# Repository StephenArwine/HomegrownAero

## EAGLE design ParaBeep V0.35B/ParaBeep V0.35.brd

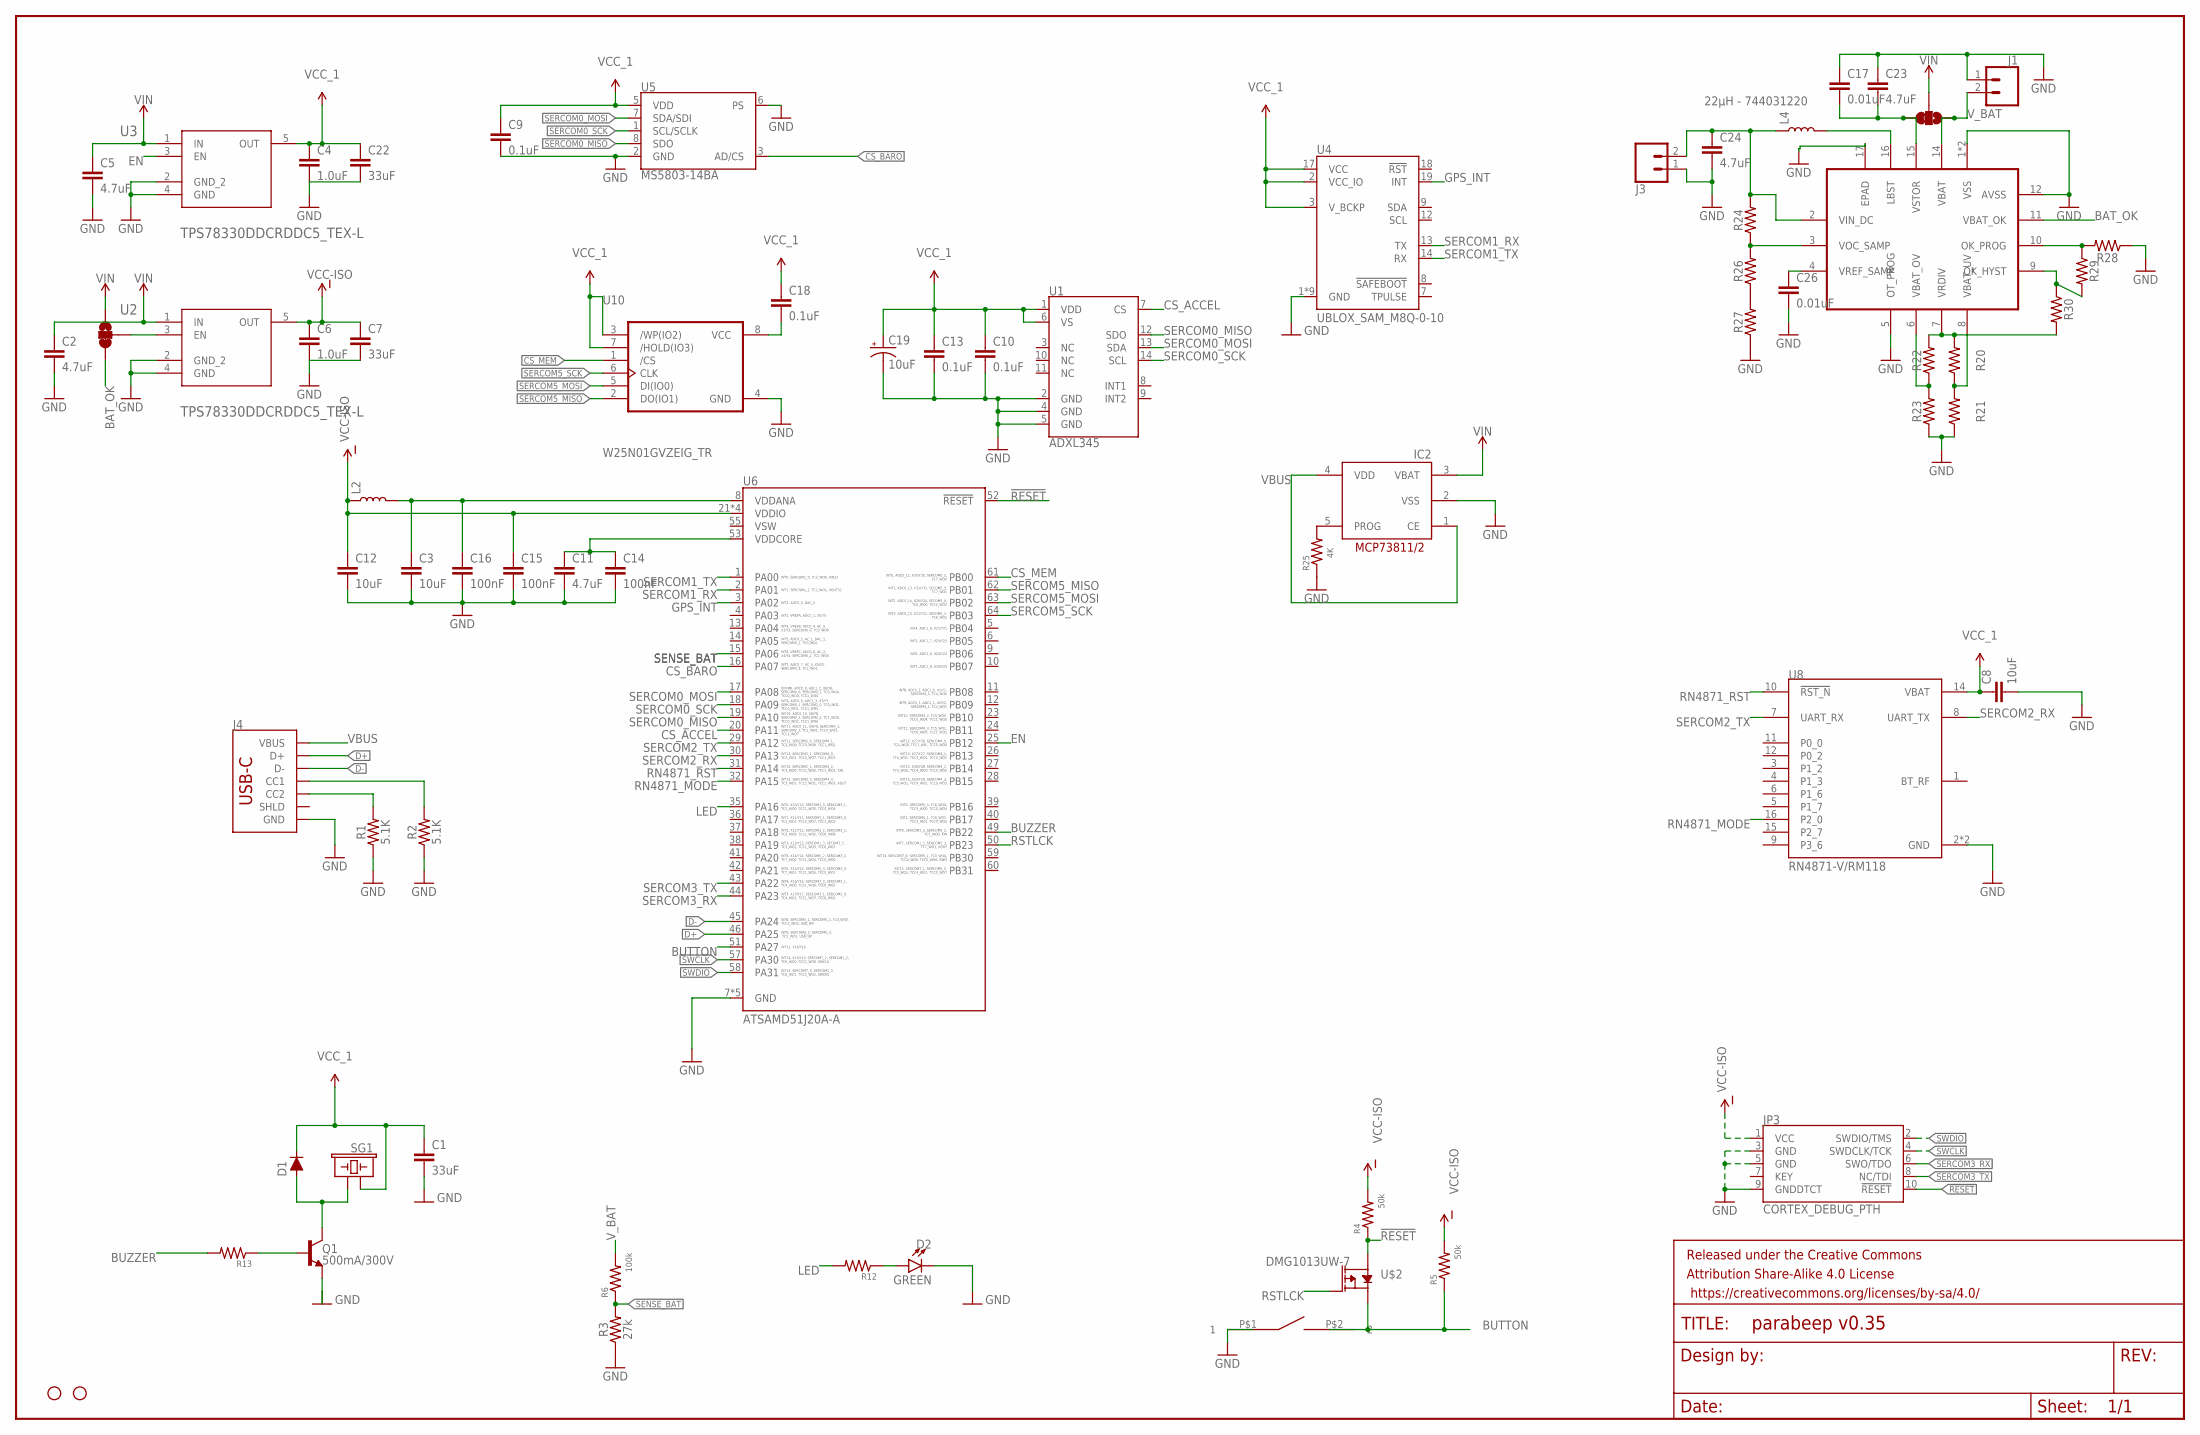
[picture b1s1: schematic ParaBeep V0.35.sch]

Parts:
C1, C7, C22: 33uF; 1206
C2, C5, C11, C24: 4.7uF; 0603
C3, C8, C12: 10uF; 0603
C4, C6: 1.0uF; 0603
C9, C10, C13, C18: 0.1uF; 0603
C14, C15, C16: 100nF; 0603
C17, C26: 0.01uF; 0402
C19: 10uF; EIA3216
C23: 4.7uF; 0402
D1: 250mA/100V; SOD-323
D2: GREEN; LED-0603
FRAME1: FRAME-LEDGER; CREATIVE_COMMONS
H1, H2: STAND-OFFTIGHT; STAND-OFF-TIGHT
IC2: MCP73811/2; SOT23-5L
J1, J3: CONN_02-JST-2MM-SMT; JST-2-SMD
J4: USB_C_2-LAYER_PADS; USB-C-16P-2LAYER-PADS
JP1, JP2: JUMPER-SMT_3_1-NC_TRACE_SILK; SMT-JUMPER_3_1-NC_TRACE_SILK
JP3: CORTEX_DEBUG_PTH; 2X5-PTH-1.27MM
L2: INDUCTORFB-30OHM; 0603
L4: 22µH - 744031220; INDUCTOR_4.7UH
Q1: 500mA/300V; SOT23-3
R1, R2: 5.1K; 0402
R3: 27k; 0402
R4, R5: 50k; 0402
R6: 100k; 0402
R12, R13, R20, R21, R22, R23, R24, R26, R27, R28, R29, R30: 0402
R25: 4K; 0402
SG1: BUZZER-SMD_KIT; BUZZER-CCV-KIT
U1: ADXL345; LGA-14
U2, U3: TPS78330DDCRDDC5_TEX-L; DDC5_TEX-L
U4: UBLOX_SAM_M8Q-0-10; SAM-M8Q
U5: MS5803-14BA; MS5803
U6: ATSAMD51J20A-A; TQFP64
U8: RN4871-V/RM118; XCVR_RN4871-V/RM118
U9: BQ25504RGTR; QFN50P300X300X100-17N
U10: W25N01GVZEIG_TR; SON127P800X600X80-9N
U$2: DMG1013UW-7
U$3: AB11AH-HC

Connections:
!RESET: JP3.10 (!RESET), R4.1, U6.52 (!RESET), U$2.2 (S)
BAT_OK: JP2.3, U9.11 (VBAT_OK)
BUTTON: R5.1, U6.51 (PA27), U$2.3 (D), U$3.P$2 (2)
BUZZER: R13.2, U6.49 (PB22)
CS_ACCEL: U1.7 (CS), U6.20 (PA11)
CS_BARO: U5.3 (AD/CS), U6.16 (PA07)
CS_MEM: U6.61 (PB00), U10.1 (/CS)
D+: J4.A6 (D+), J4.B6 (D+), U6.46 (PA25)
D-: J4.A7 (D-), J4.B7 (D-), U6.45 (PA24)
EN: U3.3 (EN), U6.25 (PB12)
GND: C1.2, C2.2, C3.2, C4.2, C5.2, C6.2, C7.2, C8.2, C9.2, C10.2, C11.2, C12.2, C13.2, C14.2, C15.2, C16.2, C17.1, C19.-, C22.2, C23.1, C24.2, C26.2, D2.C, IC2.2 (VSS), J1.1 (2), J3.1 (2), J4.GND, J4.GND2 (GND), JP3.3 (GND), JP3.5 (GND), JP3.9 (GNDDTCT), Q1.2 (E), R1.1, R2.1, R3.1, R21.1, R23.1, R25.1, R27.1, R28.1, U1.2 (GND), U1.4 (GND), U1.5 (GND), U2.2 (GND_2), U2.4 (GND), U3.2 (GND_2), U3.4 (GND), U4.1 (GND), U4.4 (GND), U4.5 (GND), U4.6 (GND), U4.10 (GND), U4.11 (GND), U4.15 (GND), U4.16 (GND), U4.20 (GND), U5.2 (GND), U5.6 (PS), U6.7 (GND), U6.22 (GND), U6.33 (GND), U6.47 (GND), U6.54 (GND), U8.2 (GND), U8.13 (GND), U9.1 (VSS), U9.5 (OT_PROG), U9.12 (AVSS), U9.13 (VSS), U9.17 (EPAD), U10.4 (GND), U$3.P$1 (1)
GPS_INT: U4.19 (INT), U6.3 (PA02)
LED: R12.2, U6.35 (PA16)
unnamed: R20.2, R22.2, R30.2, U9.7 (VRDIV)
unnamed: R20.1, R21.2, U9.8 (VBAT_UV)
unnamed: C17.2, C23.2, JP1.3, U9.15 (VSTOR)
unnamed: J4.B5 (CC2), R1.2
unnamed: J4.A5 (CC1), R2.2
unnamed: JP2.2, U2.3 (EN)
unnamed: D1.A, Q1.3 (C), SG1.- (2)
unnamed: Q1.1 (B), R13.1
unnamed: C18.2, U10.8 (VCC)
unnamed: D2.A, R12.1
unnamed: IC2.5 (PROG), R25.2
unnamed: C11.1, C14.1, U6.53 (VDDCORE)
unnamed: R22.1, R23.2, U9.6 (VBAT_OV)
unnamed: R29.2, R30.1, U9.9 (OK_HYST)
unnamed: R28.2, R29.1, U9.10 (OK_PROG)
unnamed: C3.1, C16.1, L2.2, U6.8 (VDDANA)
unnamed: C26.1, U9.4 (VREF_SAMP)
unnamed: R24.1, R26.2, U9.3 (VOC_SAMP)
unnamed: C24.1, J3.2 (1), L4.P$1 (1), R24.2, U9.2 (VIN_DC)
unnamed: L4.P$2 (2), U9.16 (LBST)
unnamed: R26.1, R27.2
RN4871_MODE: U6.32 (PA15), U8.16 (P2_0)
RN4871_RST: U6.31 (PA14), U8.10 (!RST_N)
RSTLCK: U6.50 (PB23), U$2.1 (G)
SENSE_BAT: R3.2, R6.1, U6.15 (PA06)
SERCOM0_MISO: U1.12 (SDO), U5.8 (SDO), U6.19 (PA10)
SERCOM0_MOSI: U1.13 (SDA), U5.7 (SDA/SDI), U6.17 (PA08)
SERCOM0_SCK: U1.14 (SCL), U5.1 (SCL/SCLK), U6.18 (PA09)
SERCOM1_RX: U4.13 (TX), U6.2 (PA01)
SERCOM1_TX: U4.14 (RX), U6.1 (PA00)
SERCOM2_RX: U6.30 (PA13), U8.8 (UART_TX)
SERCOM2_TX: U6.29 (PA12), U8.7 (UART_RX)
SERCOM3_RX: JP3.6 (SWO/TDO), U6.44 (PA23)
SERCOM3_TX: JP3.8 (NC/TDI), U6.43 (PA22)
SERCOM5_MISO: U6.62 (PB01), U10.2 (DO(IO1))
SERCOM5_MOSI: U6.63 (PB02), U10.5 (DI(IO0))
SERCOM5_SCK: U6.64 (PB03), U10.6 (CLK)
SWCLK: JP3.4 (SWDCLK/TCK), U6.57 (PA30)
SWDIO: JP3.2 (SWDIO/TMS), U6.58 (PA31)
VBUS: IC2.1 (CE), IC2.4 (VDD), J4.VBUS1 (VBUS), J4.VBUS2 (VBUS)
VCC-ISO: C6.1, C7.1, C12.1, C15.1, JP3.1 (VCC), L2.1, R4.2, R5.2, U2.5 (OUT), U6.21 (VDDIO), U6.34 (VDDIO), U6.48 (VDDIO), U6.56 (VDDIO)
VCC_1: C1.1, C4.1, C8.1, C9.1, C10.1, C13.1, C18.1, C19.+, C22.1, D1.C, SG1.+ (1), U1.1 (VDD), U1.6 (VS), U3.5 (OUT), U4.2 (VCC_IO), U4.3 (V_BCKP), U4.17 (VCC), U5.5 (VDD), U8.14 (VBAT), U10.3 (/WP(IO2)), U10.7 (/HOLD(IO3))
VIN: C2.1, C5.1, IC2.3 (VBAT), JP1.2, JP2.1, U2.1 (IN), U3.1 (IN)
V_BAT: J1.2 (1), JP1.1, R6.2, U9.14 (VBAT)

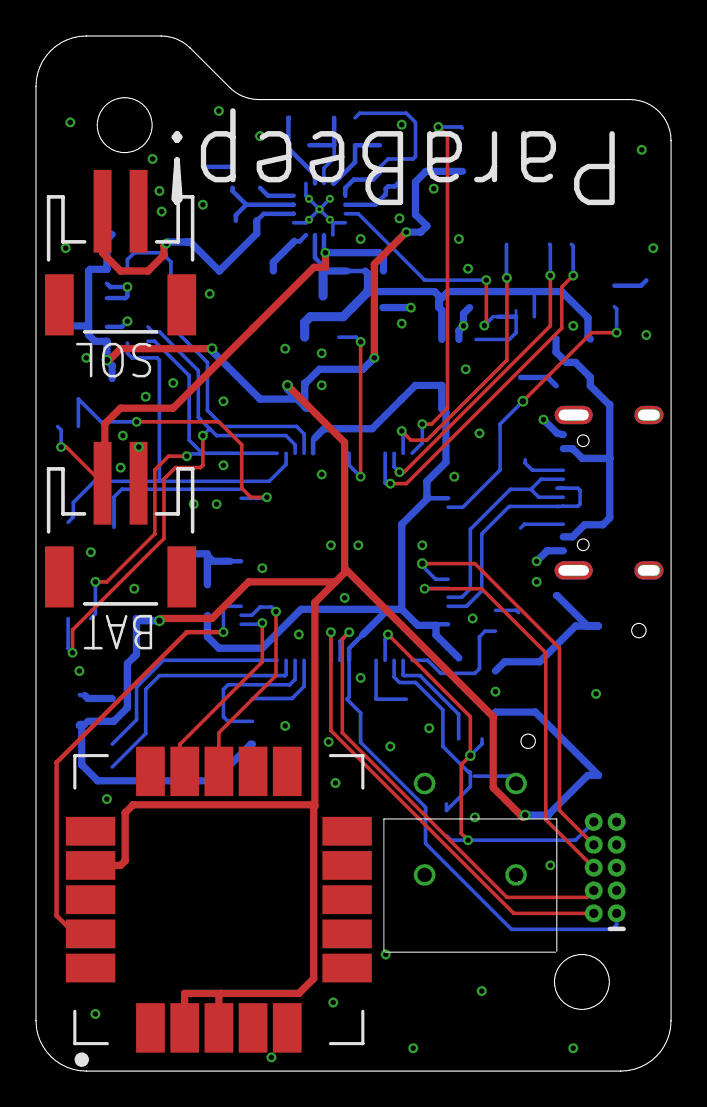
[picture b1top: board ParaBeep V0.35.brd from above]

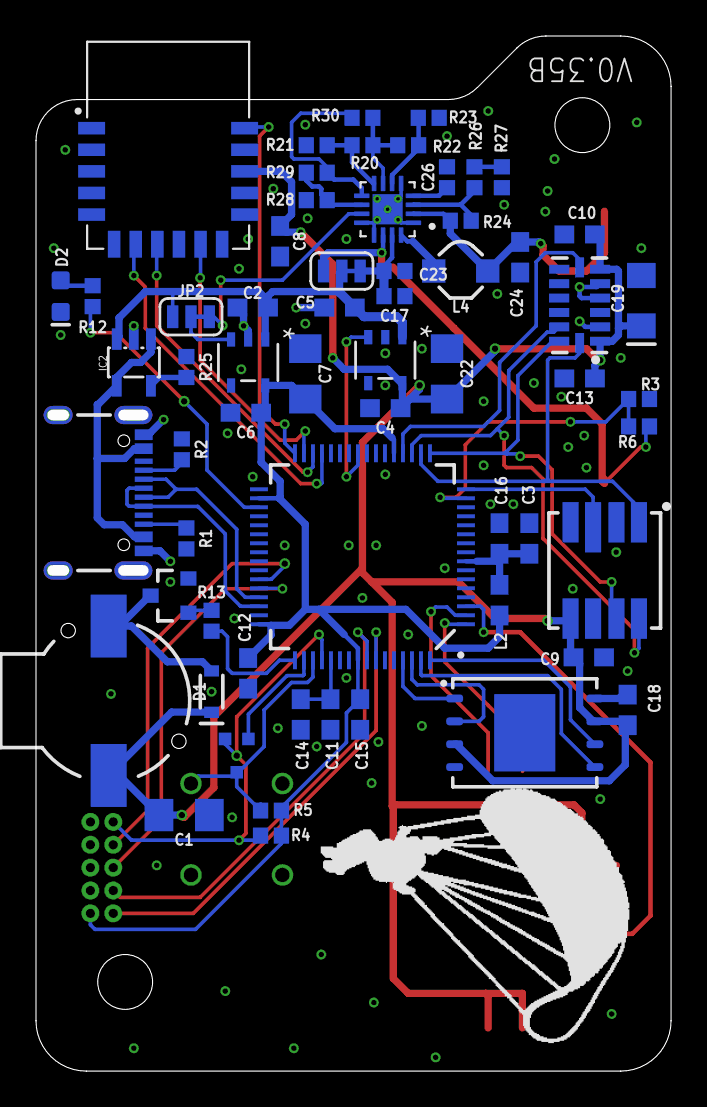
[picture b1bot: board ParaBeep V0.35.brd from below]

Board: 2 copper layers, 35.3 x 57.5 mm, 70 parts (62 on the bottom side), 57 nets.

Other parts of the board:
U$5: PARA

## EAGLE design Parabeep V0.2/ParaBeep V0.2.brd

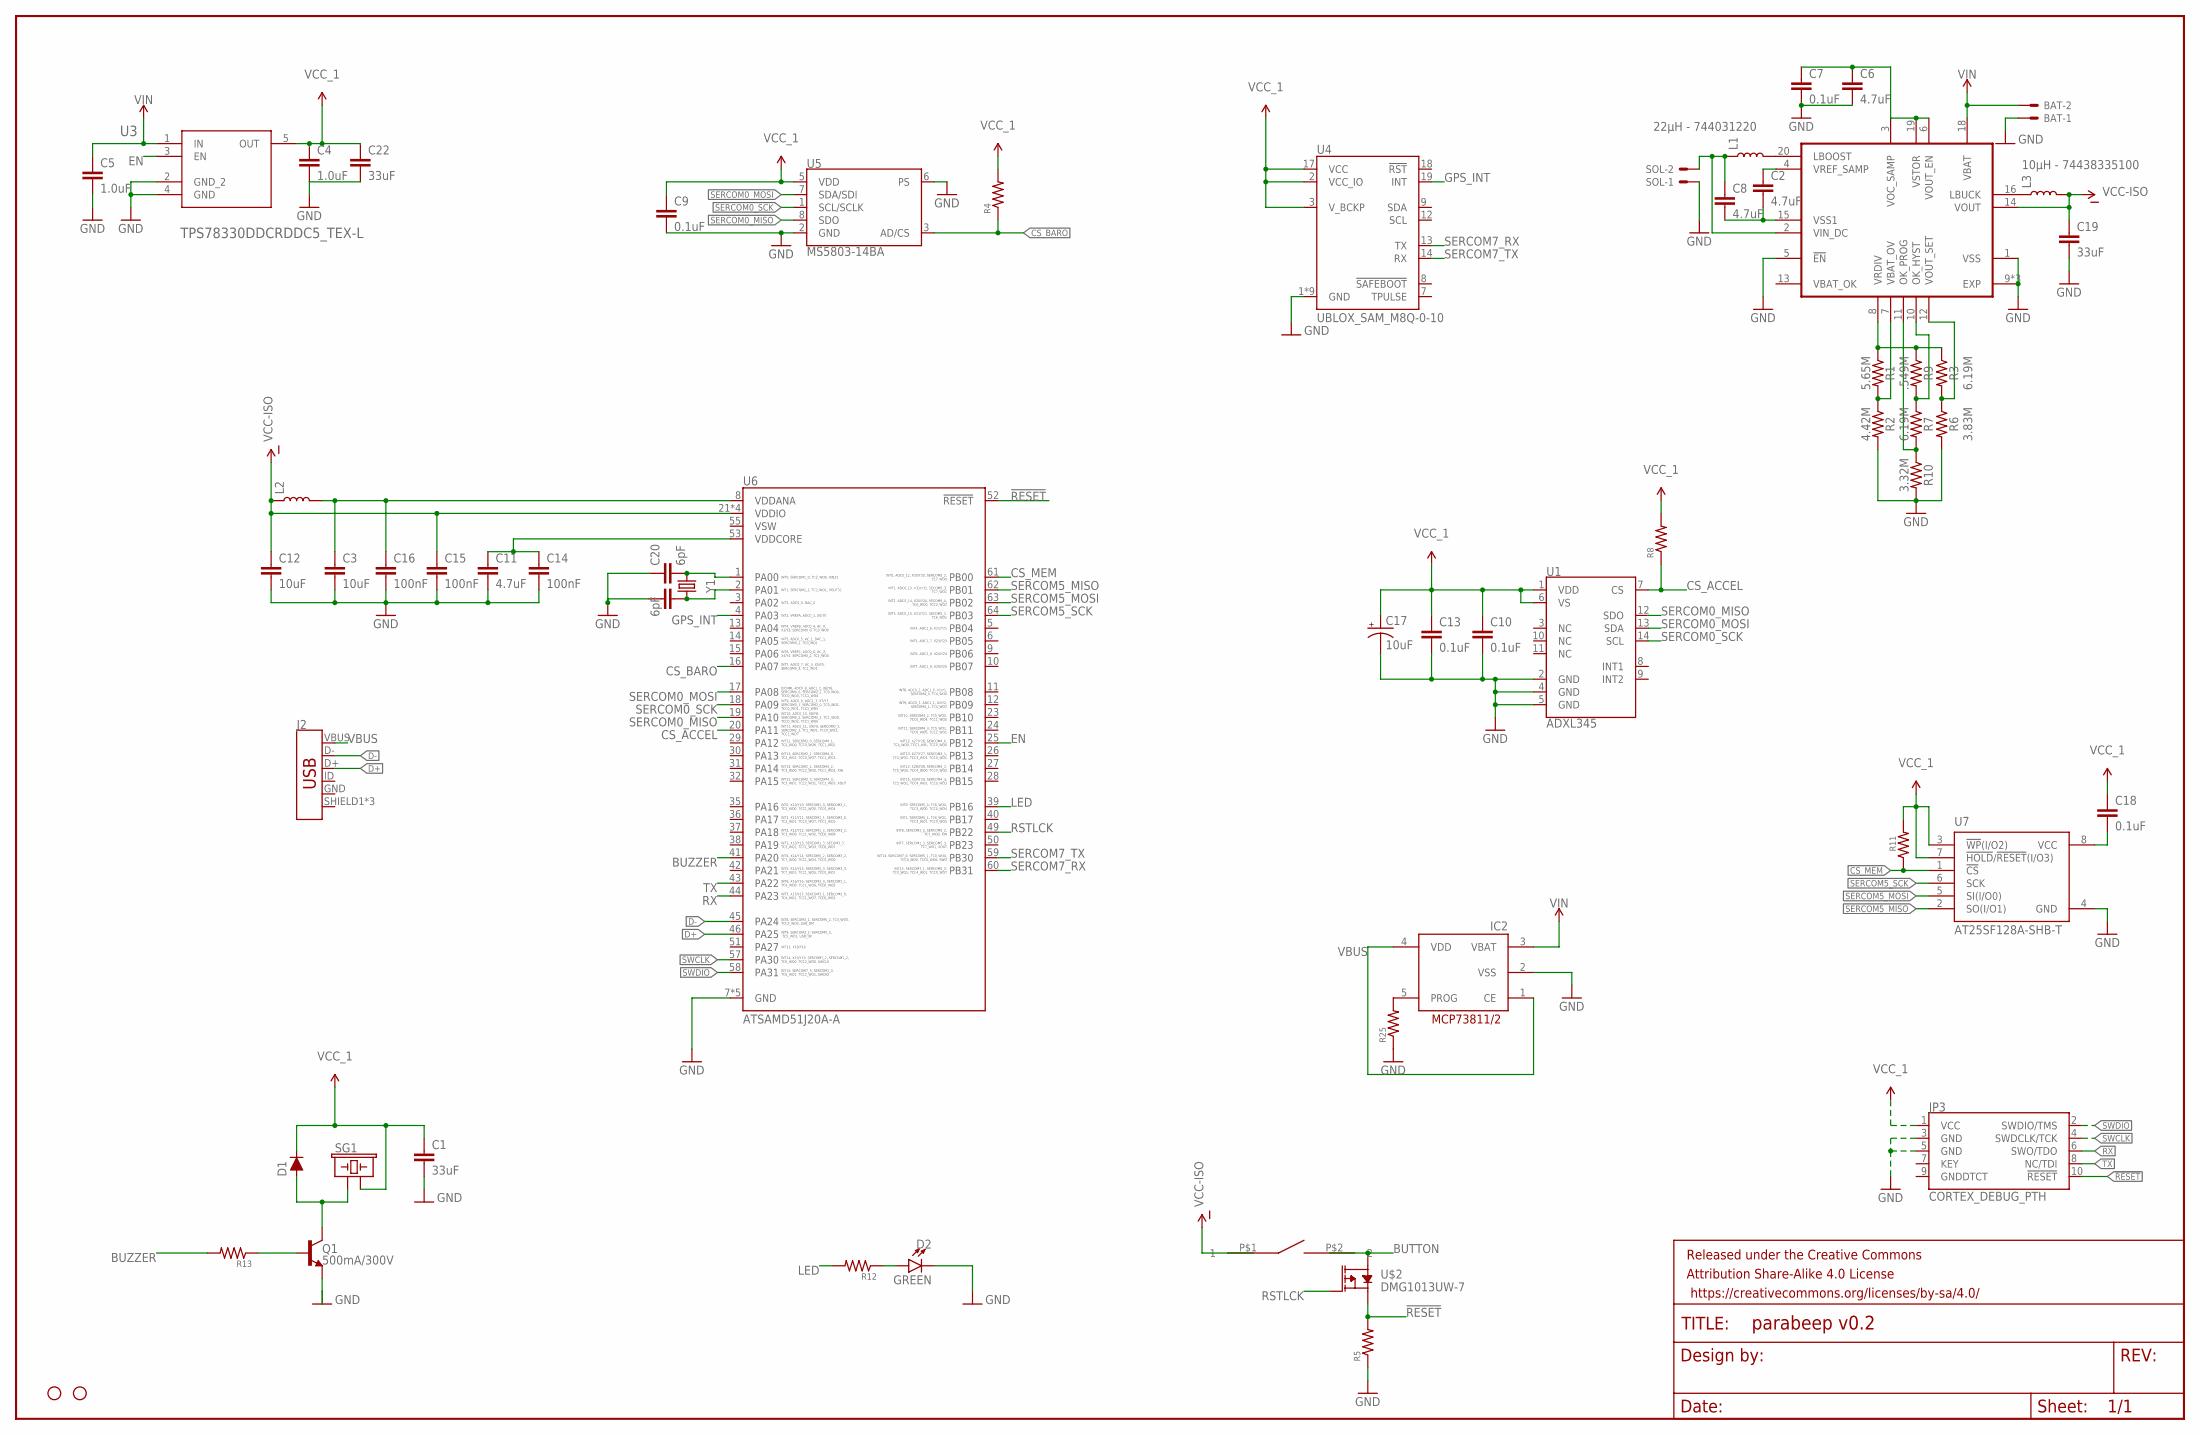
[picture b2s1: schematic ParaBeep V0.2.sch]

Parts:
BAT: SM02B-SSR-H-TB
C1, C19, C22: 33uF; 1206
C2, C6, C8, C11: 4.7uF; 0603
C3, C12: 10uF; 0603
C4, C5: 1.0uF; 0603
C7, C9, C10, C13, C18: 0.1uF; 0603
C14, C15, C16: 100nF; 0603
C17: 10uF; 0603-POLAR
C20, C21: 6pF; 0402
D1: 250mA/100V; SOD-323
D2: GREEN; LED-0603
FRAME1: FRAME-LEDGER; CREATIVE_COMMONS
H1, H2: STAND-OFFTIGHT; STAND-OFF-TIGHT
IC2: MCP73811/2; SOT23-5L
J2: USB_MICRO-B_FEMALE-SMT; USB-B-MICRO-SMD
JP3: CORTEX_DEBUG_PTH; 2X5-PTH-1.27MM
L1: 22µH - 744031220; INDUCTOR_4.7UH
L2: INDUCTORFB-30OHM; 0603
L3: 10µH - 74438335100; INDUCTOR_4.7UH
Q1: 500mA/300V; SOT23-3
R1: 5.65M; 0603
R2: 4.42M; 0603
R3, R7: 6.19M; 0603
R4, R5, R8, R11, R12, R13, R25: 0402
R6: 3.83M; 0603
R9: .549M; 0603
R10: 3.32M; 0603
SG1: BUZZER-SMD_KIT; BUZZER-CCV-KIT
SOL: SM02B-SSR-H-TB
U1: ADXL345; LGA-14
U2: BQ25570RGRR; QFN50P350X350X100-21N
U3: TPS78330DDCRDDC5_TEX-L; DDC5_TEX-L
U4: UBLOX_SAM_M8Q-0-10; SAM-M8Q
U5: MS5803-14BA; MS5803
U6: ATSAMD51J20A-A; TQFP64
U7: AT25SF128A-SHB-T; SOIC127P790X216-8N
U$2: DMG1013UW-7
U$3: AB11AH-HC
Y1: 32.768kHz; CRYSTAL-SMD-3.2X1.5MM

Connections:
!RESET: JP3.10 (!RESET), R5.2, U6.52 (!RESET), U$2.3 (D)
BUTTON: U$2.2 (S), U$3.P$2 (2)
BUZZER: R13.2, U6.41 (PA20)
CS_ACCEL: R8.1, U1.7 (CS), U6.20 (PA11)
CS_BARO: R4.1, U5.3 (AD/CS), U6.16 (PA07)
CS_MEM: R11.1, U6.61 (PB00), U7.1 (!CS)
D+: J2.D+, U6.46 (PA25)
D-: J2.D-, U6.45 (PA24)
EN: U3.3 (EN), U6.25 (PB12)
GND: BAT.1, C1.2, C3.2, C4.2, C5.2, C6.2, C7.2, C9.2, C10.2, C11.2, C12.2, C13.2, C14.2, C15.2, C16.2, C17.-, C19.2, C20.1, C21.1, C22.2, D2.C, IC2.2 (VSS), J2.GND, JP3.3 (GND), JP3.5 (GND), Q1.2 (E), R2.2, R5.1, R6.2, R10.2, R25.1, SOL.1, U1.2 (GND), U1.4 (GND), U1.5 (GND), U2.1 (VSS), U2.5 (!EN), U2.9 (EXP), U2.17 (EXP), U2.21 (EXP), U3.2 (GND_2), U3.4 (GND), U4.1 (GND), U4.4 (GND), U4.5 (GND), U4.6 (GND), U4.10 (GND), U4.11 (GND), U4.15 (GND), U4.16 (GND), U4.20 (GND), U5.2 (GND), U5.6 (PS), U6.7 (GND), U6.22 (GND), U6.33 (GND), U6.47 (GND), U6.54 (GND), U7.4 (GND)
GPS_INT: U4.19 (INT), U6.4 (PA03)
LED: R12.2, U6.39 (PB16)
unnamed: C20.2, U6.1 (PA00), Y1.P$2 (2)
unnamed: C21.2, U6.2 (PA01), Y1.P$1 (1)
unnamed: R1.1, R3.1, R9.1, U2.8 (VRDIV)
unnamed: C2.1, U2.4 (VREF_SAMP)
unnamed: R7.2, R10.1, U2.11 (OK_PROG)
unnamed: R3.2, R6.1, U2.12 (VOUT_SET)
unnamed: R7.1, R9.2, U2.10 (OK_HYST)
unnamed: R1.2, R2.1, U2.7 (VBAT_OV)
unnamed: C2.2, C8.2, U2.15 (VSS1)
unnamed: D1.A, Q1.3 (C), SG1.+ (1)
unnamed: C8.1, L1.P$1 (1), SOL.2, U2.2 (VIN_DC)
unnamed: L3.P$1 (1), U2.16 (LBUCK)
unnamed: Q1.1 (B), R13.1
unnamed: C18.2, U7.8 (VCC)
unnamed: L1.P$2 (2), U2.20 (LBOOST)
unnamed: C6.1, C7.1, U2.3 (VOC_SAMP), U2.6 (VOUT_EN), U2.19 (VSTOR)
unnamed: D2.A, R12.1
unnamed: IC2.5 (PROG), R25.2
unnamed: C11.1, C14.1, U6.53 (VDDCORE)
unnamed: C3.1, C16.1, L2.2, U6.8 (VDDANA)
RSTLCK: U6.49 (PB22), U$2.1 (G)
RX: JP3.6 (SWO/TDO), U6.44 (PA23)
SERCOM0_MISO: U1.12 (SDO), U5.8 (SDO), U6.19 (PA10)
SERCOM0_MOSI: U1.13 (SDA), U5.7 (SDA/SDI), U6.17 (PA08)
SERCOM0_SCK: U1.14 (SCL), U5.1 (SCL/SCLK), U6.18 (PA09)
SERCOM5_MISO: U6.62 (PB01), U7.2 (SO(I/O1))
SERCOM5_MOSI: U6.63 (PB02), U7.5 (SI(I/O0))
SERCOM5_SCK: U6.64 (PB03), U7.6 (SCK)
SERCOM7_RX: U4.13 (TX), U6.60 (PB31)
SERCOM7_TX: U4.14 (RX), U6.59 (PB30)
SWCLK: JP3.4 (SWDCLK/TCK), U6.57 (PA30)
SWDIO: JP3.2 (SWDIO/TMS), U6.58 (PA31)
TX: JP3.8 (NC/TDI), U6.43 (PA22)
VBUS: IC2.1 (CE), IC2.4 (VDD), J2.VBUS
VCC-ISO: C12.1, C15.1, C19.1, L2.1, L3.P$2 (2), U2.14 (VOUT), U6.21 (VDDIO), U6.34 (VDDIO), U6.48 (VDDIO), U6.56 (VDDIO), U$3.P$1 (1)
VCC_1: C1.1, C4.1, C9.1, C10.1, C13.1, C17.+, C18.1, C22.1, D1.C, JP3.1 (VCC), R4.2, R8.2, R11.2, SG1.- (2), U1.1 (VDD), U1.6 (VS), U3.5 (OUT), U4.2 (VCC_IO), U4.3 (V_BCKP), U4.17 (VCC), U5.5 (VDD), U7.3 (!WP!(I/O2)), U7.7 (!HOLD!/!RESET!(I/O3))
VIN: BAT.2, C5.1, IC2.3 (VBAT), U2.18 (VBAT), U3.1 (IN)

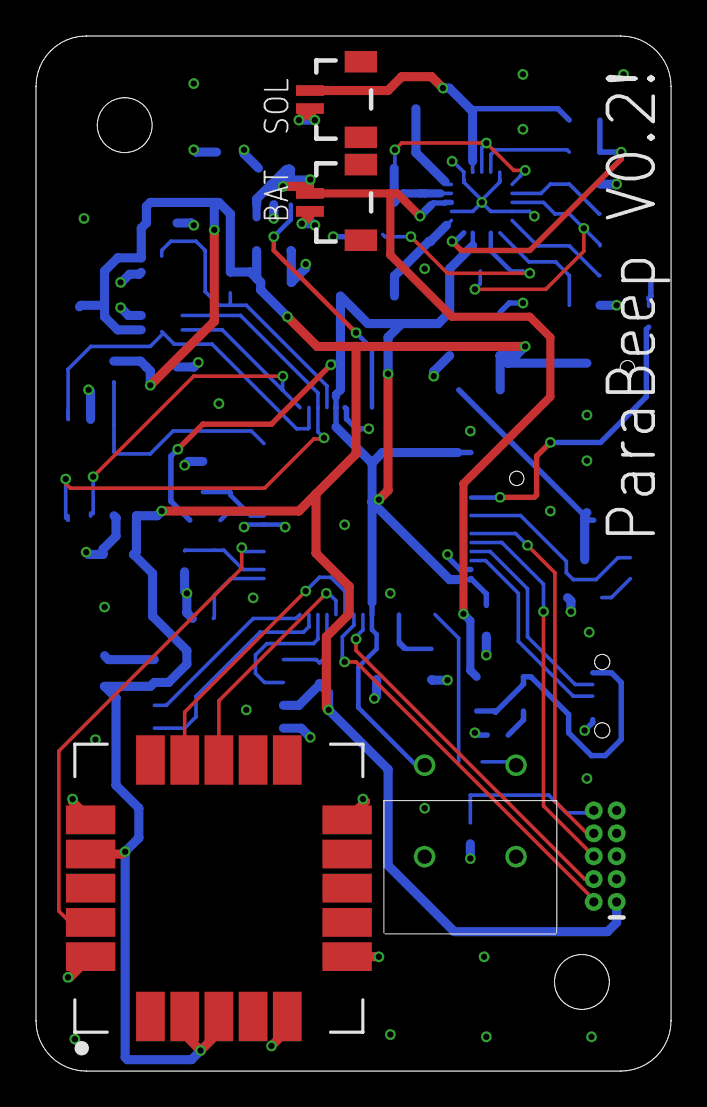
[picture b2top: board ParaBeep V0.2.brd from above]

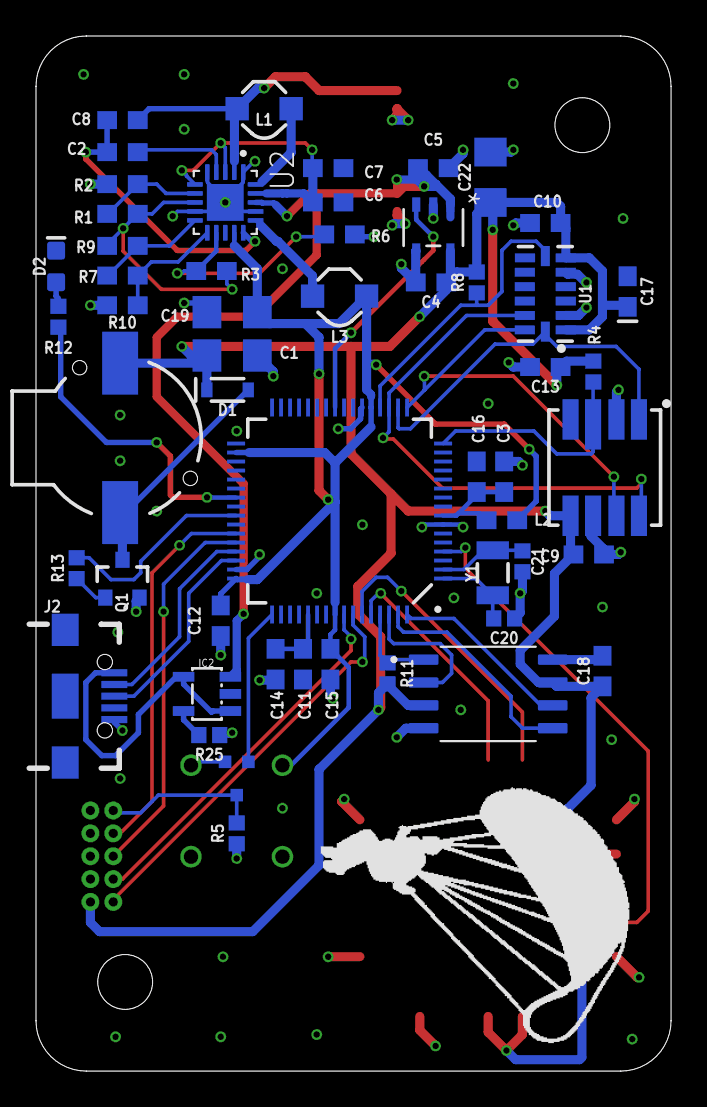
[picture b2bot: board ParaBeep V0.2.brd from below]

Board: 2 copper layers, 35.3 x 57.5 mm, 62 parts (54 on the bottom side), 49 nets.

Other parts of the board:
U$5: PARA

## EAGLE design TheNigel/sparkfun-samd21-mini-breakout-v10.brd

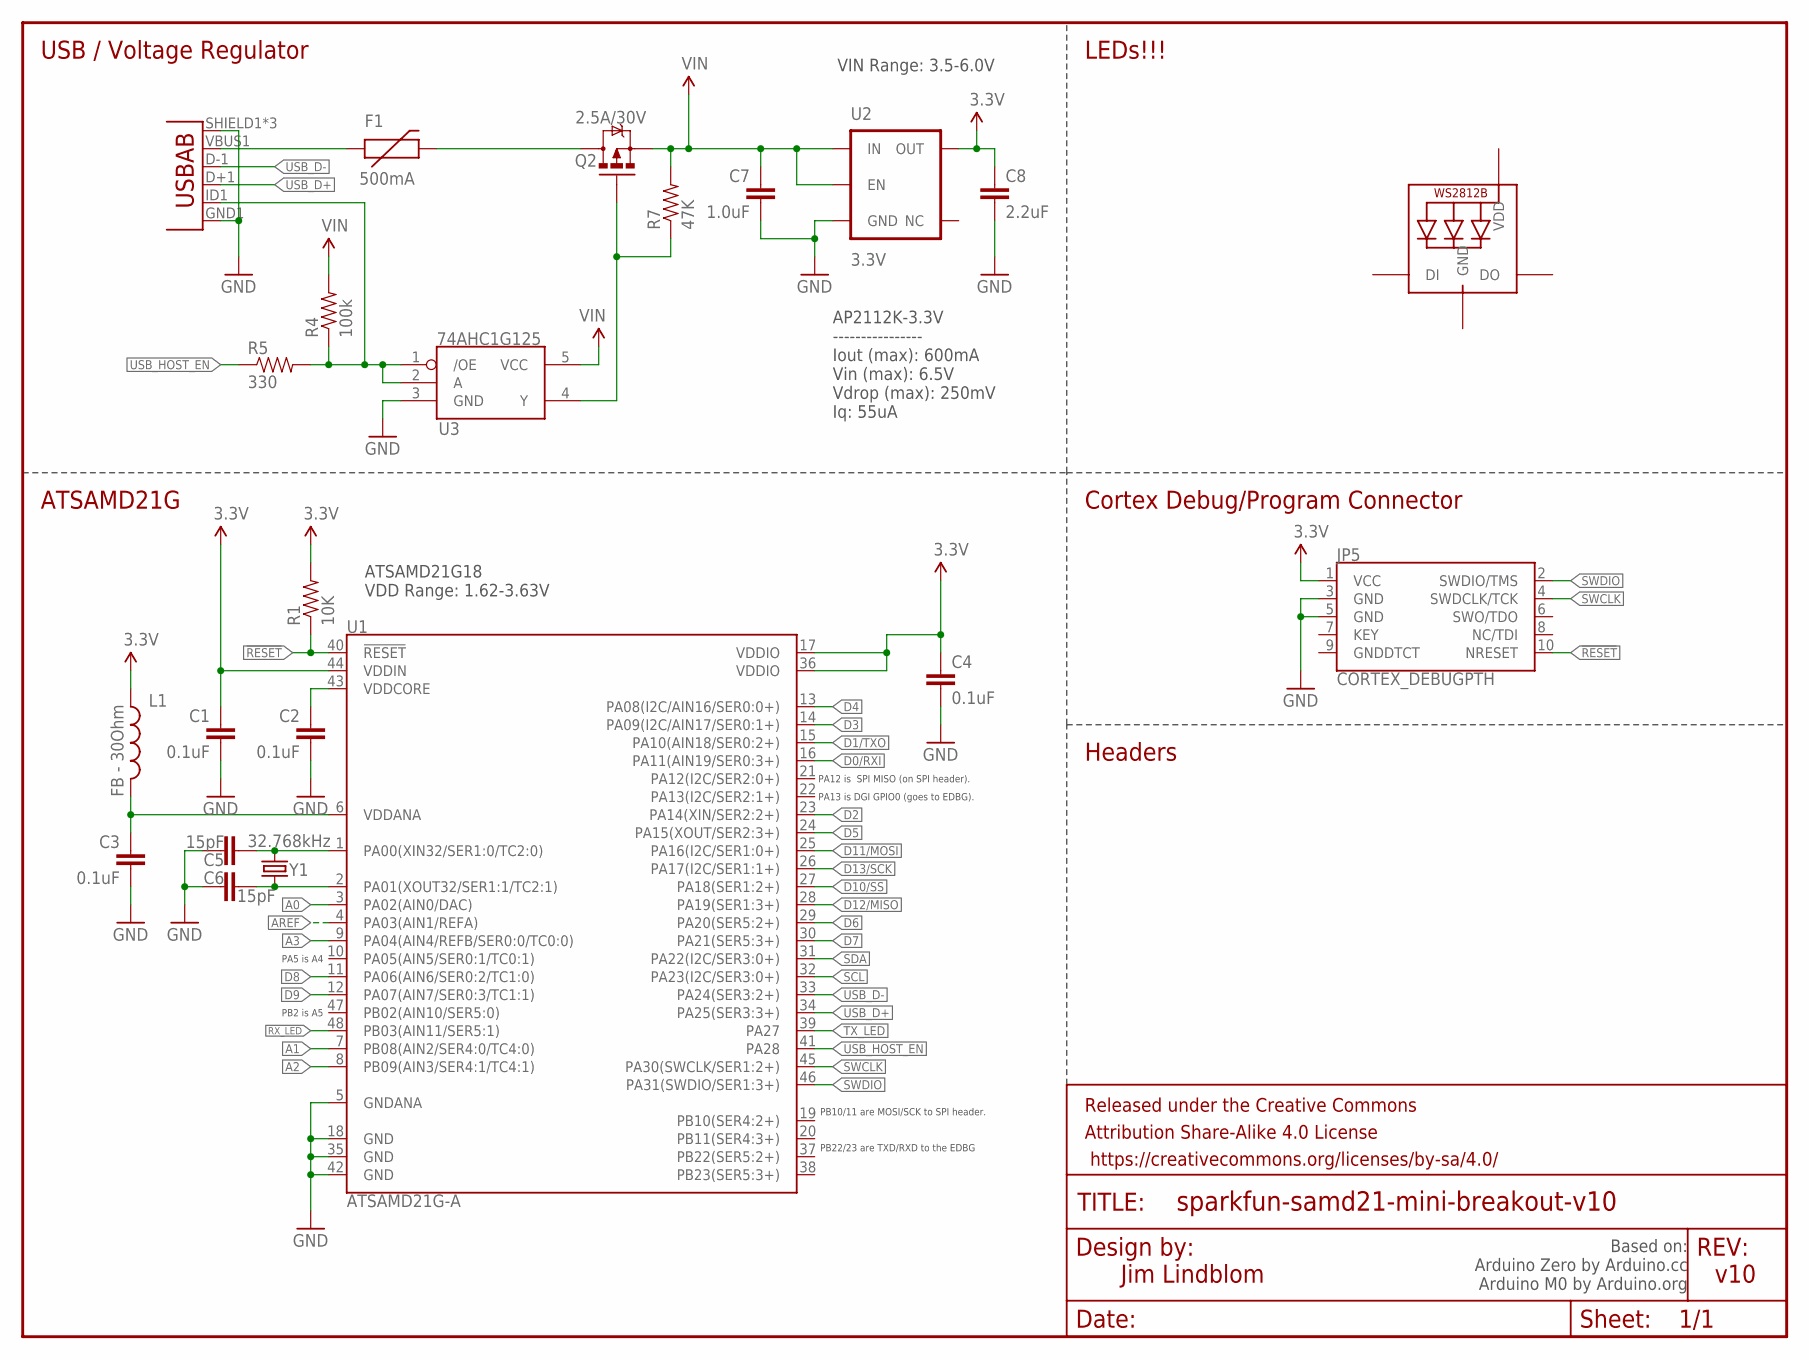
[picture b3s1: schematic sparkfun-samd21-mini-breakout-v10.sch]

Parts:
C1, C2, C3, C4: 0.1uF; 0402-CAP
C5, C6: 15pF; 0402-CAP
C7: 1.0uF; 0805-CAP
C8: 2.2uF; 0603-CAP
F1: 500mA; PTC-1206
FRAME1: FRAME-LETTER; CREATIVE_COMMONS
JP3: USB-ABCONN-11794; USB-AB-MICRO-SMD_V03
JP5: CORTEX_DEBUGPTH; 2X5-PTH-1.27MM
L1: FB - 30Ohm; 0603
LED1: WS2812B3535; LED3535
Q2: 2.5A/30V; SOT23-3
R1: 10K; 0603-RES
R4: 100k; 0603-RES
R5: 330; 0603-RES
R7: 47K; 0603-RES
U1: ATSAMD21G-A; TQFP-48
U2: 3.3V; SOT23-5
U3: 74AHC1G125; SOT23-5
Y1: 32.768kHz; CRYSTAL-SMD-3.2X1.5MM

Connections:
3.3V: C1.1, C4.1, C8.1, JP5.1 (VCC), L1.1, R1.2, U1.17 (VDDIO), U1.36 (VDDIO), U1.44 (VDDIN), U2.5 (OUT)
!RESET: JP5.10 (NRESET), R1.1, U1.40 (!RESET!)
A0: U1.3 (PA02(AIN0/DAC))
A1: U1.7 (PB08(AIN2/SER4:0/TC4:0))
A2: U1.8 (PB09(AIN3/SER4:1/TC4:1))
A3: U1.9 (PA04(AIN4/REFB/SER0:0/TC0:0))
AREF: U1.4 (PA03(AIN1/REFA))
D0/RXI: U1.16 (PA11(AIN19/SER0:3+))
D1/TXO: U1.15 (PA10(AIN18/SER0:2+))
D2: U1.23 (PA14(XIN/SER2:2+))
D3: U1.14 (PA09(I2C/AIN17/SER0:1+))
D4: U1.13 (PA08(I2C/AIN16/SER0:0+))
D5: U1.24 (PA15(XOUT/SER2:3+))
D6: U1.29 (PA20(SER5:2+))
D7: U1.30 (PA21(SER5:3+))
D8: U1.11 (PA06(AIN6/SER0:2/TC1:0))
D9: U1.12 (PA07(AIN7/SER0:3/TC1:1))
D10/SS: U1.27 (PA18(SER1:2+))
D11/MOSI: U1.25 (PA16(I2C/SER1:0+))
D12/MISO: U1.28 (PA19(SER1:3+))
D13/SCK: U1.26 (PA17(I2C/SER1:1+))
GND: C1.2, C2.2, C3.2, C4.2, C5.1, C6.2, C7.2, C8.2, JP3.GND1 (GND), JP3.SHIELD1 (SHIELD), JP3.SHIELD2 (SHIELD), JP3.SHIELD3 (SHIELD), JP5.3 (GND), JP5.5 (GND), LED1.4 (GND), U1.5 (GNDANA), U1.18 (GND), U1.35 (GND), U1.42 (GND), U2.2 (GND), U3.3 (GND)
unnamed: F1.1, JP3.VBUS1 (VBUS)
unnamed: C5.2, U1.1 (PA00(XIN32/SER1:0/TC2:0)), Y1.P$2 (2)
unnamed: C6.1, U1.2 (PA01(XOUT32/SER1:1/TC2:1)), Y1.P$1 (1)
unnamed: F1.2, Q2.3 (D)
unnamed: JP3.ID1 (USBID), R4.1, R5.2, U3.1 (/OE), U3.2 (A)
unnamed: Q2.1 (G), R7.1, U3.4 (Y)
RX_LED: U1.48 (PB03(AIN11/SER5:1))
SCL: U1.32 (PA23(I2C/SER3:0+))
SDA: U1.31 (PA22(I2C/SER3:0+))
SWCLK: JP5.4 (SWDCLK/TCK), U1.45 (PA30(SWCLK/SER1:2+))
SWDIO: JP5.2 (SWDIO/TMS), U1.46 (PA31(SWDIO/SER1:3+))
TX_LED: U1.39 (PA27)
USB_D+: JP3.D+1 (D+), U1.34 (PA25(SER3:3+))
USB_D-: JP3.D-1 (D-), U1.33 (PA24(SER3:2+))
USB_HOST_EN: R5.1, U1.41 (PA28)
VDD: LED1.2 (VDD)
VDDANA: C3.1, L1.2, U1.6 (VDDANA)
VDDCORE: C2.1, U1.43 (VDDCORE)
VIN: C7.1, Q2.2 (S), R4.2, R7.2, U2.1 (IN), U2.3 (EN), U3.5 (VCC)

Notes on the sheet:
PB22/23 are TXD/RXD to the EDBG
PB10/11 are MOSI/SCK to SPI header.
PA12 is SPI MISO (on SPI header).
PA13 is DGI GPIO0 (goes to EDBG).
PA5 is A4
PB2 is A5
USB / Voltage Regulator
LEDs!!!
Cortex Debug/Program Connector
Headers
ATSAMD21G
Jim Lindblom
v10
ATSAMD21G18 VDD Range: 1.62-3.63V
VIN Range: 3.5-6.0V
Based on: Arduino Zero by Arduino.cc Arduino M0 by Arduino.org
AP2112K-3.3V ---------------- Iout (max): 600mA Vin (max): 6.5V Vdrop (max): 250mV Iq: 55uA

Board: 4 copper layers, 23 parts (0 on the bottom side), 17 nets, no tracks yet.

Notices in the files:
parts and their libraries:
SparkFun-Capacitors: Licensing: Creative Commons ShareAlike 4.0 International - https://creativecommons.org/licenses/by-sa/4.0
SparkFun-Aesthetics: Released under the Creative Commons Attribution Share-Alike 4.0 License
SparkFun-Aesthetics: https://creativecommons.org/licenses/by-sa/4.0
